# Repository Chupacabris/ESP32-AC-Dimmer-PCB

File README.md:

# ESP32-AC-Dimmer-PCB

Kicad project for ESP32-based PCB board designed to dim three AC outputs using triacs triggered at a set time after zero-crossing detection (ZCD).

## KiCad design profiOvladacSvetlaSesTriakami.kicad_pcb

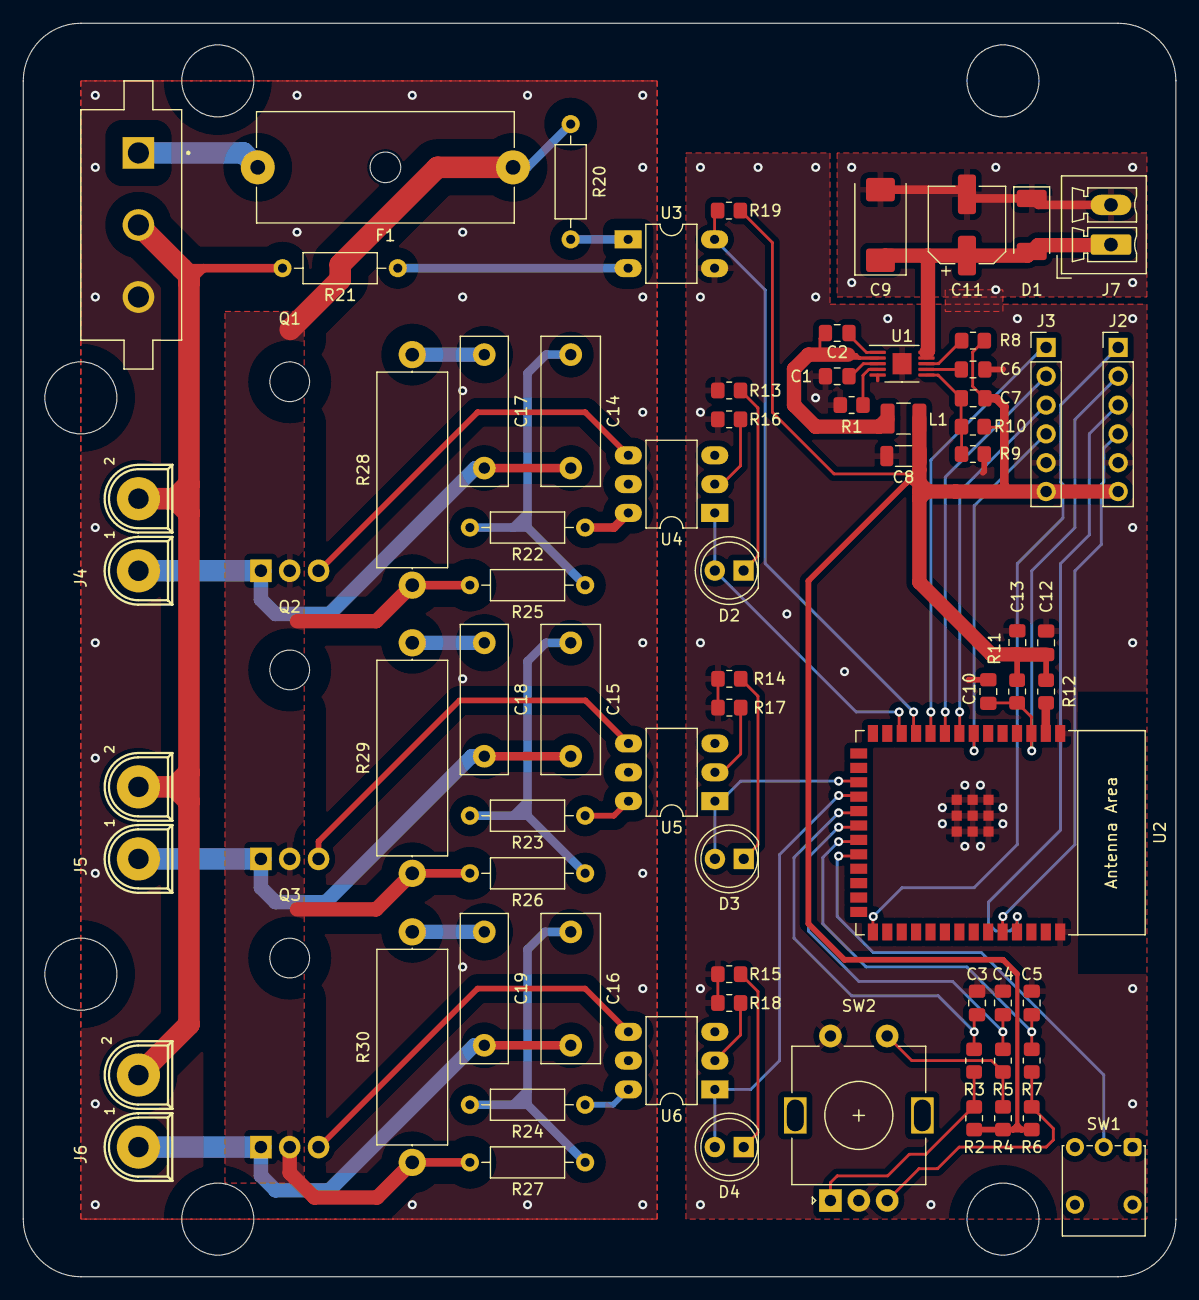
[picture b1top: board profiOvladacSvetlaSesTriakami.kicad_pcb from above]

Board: 2 copper layers, 101.6 x 110.5 mm, 73 parts (0 on the bottom side), 56 nets.

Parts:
C1: 1uF/10V; C_0805_2012Metric_Pad1.18x1.45mm_HandSolder
C2: 0.1uF/10V; C_0805_2012Metric_Pad1.18x1.45mm_HandSolder
C3, C4, C5: 10n; C_0805_2012Metric_Pad1.18x1.45mm_HandSolder
C6: 10nF/10V; C_0805_2012Metric_Pad1.18x1.45mm_HandSolder
C7: 10pF; C_0805_2012Metric_Pad1.18x1.45mm_HandSolder
C8: 22uF/X7R; C_1206_3216Metric
C9: 4.7u; CP_EIA-7343-15_Kemet-W
C10: 1uF; C_0805_2012Metric_Pad1.18x1.45mm_HandSolder
C11: 100u; CP_Elec_6.3x7.7
C12: 10uF; C_0805_2012Metric_Pad1.18x1.45mm_HandSolder
C13: 0.1uF; C_0805_2012Metric_Pad1.18x1.45mm_HandSolder
C14, C15, C16: 0.05uF; C_Rect_L13.0mm_W5.0mm_P10.00mm_FKS3_FKP3_MKS4
C17, C18, C19: 0.01uF; C_Rect_L13.0mm_W4.0mm_P10.00mm_FKS3_FKP3_MKS4
D1: DIODE; D_2010_5025Metric_Pad1.52x2.65mm_HandSolder
D2, D3, D4: LED; LED_D5.0mm
F1: Fuse; Fuseholder_Cylinder-5x20mm_Schurter_0031_8201_Horizontal_Op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
J1: 350429-1; TE_350429-1
J2: programovaci; PinHeader_1x06_P2.54mm_Vertical
J3: GPIOs; PinHeader_1x06_P2.54mm_Vertical
J4, J5, J6: 350428-1
J7: Conn_01x02_Socket; PhoenixContact_MCV_1,5_2-G-3.5_1x02_P3.50mm_Vertical
L1: 2.2uH; L_1210_3225Metric
Q1, Q2, Q3: BT138; TO-220-3_Horizontal_TabDown
R1: 18.2k; R_0805_2012Metric_Pad1.20x1.40mm_HandSolder
R2, R3, R4, R5, R6, R7, R11, R19: 10k; R_0805_2012Metric_Pad1.20x1.40mm_HandSolder
R8: 100k; R_0805_2012Metric_Pad1.20x1.40mm_HandSolder
R9: 309K; R_0805_2012Metric_Pad1.20x1.40mm_HandSolder
R10: 1M; R_0805_2012Metric_Pad1.20x1.40mm_HandSolder
R12: 0; R_0805_2012Metric_Pad1.20x1.40mm_HandSolder
R13, R14, R15, R16, R17, R18: 470; R_0805_2012Metric_Pad1.20x1.40mm_HandSolder
R20, R21: 33k; R_Axial_DIN0207_L6.3mm_D2.5mm_P10.16mm_Horizontal
R22, R23, R24: 360; R_Axial_DIN0207_L6.3mm_D2.5mm_P10.16mm_Horizontal
R25, R26, R27: 470; R_Axial_DIN0207_L6.3mm_D2.5mm_P10.16mm_Horizontal
R28, R29, R30: 39; R_Axial_DIN0617_L17.0mm_D6.0mm_P20.32mm_Horizontal
SW1: SW_SPDT; SW_Push_1P2T_Vertical_E-Switch_800UDP8P1A1M6
SW2: RotaryEncoder_Switch; RotaryEncoder_Alps_EC11E-Switch_Vertical_H20mm
U1: LT8608; MSOP-10-1EP_3x3mm_P0.5mm_EP1.68x1.88mm
U2: ESP32-S3-WROOM-1
U3: LTV-814; DIP-4_W7.62mm_LongPads
U4, U5, U6: MOC3021M; DIP-6_W7.62mm_LongPads

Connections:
+3.3V: C7.2, C8.1, C12.2, C13.1, J2.6, J3.6, L1.1, R2.1, R4.1, R6.1, R8.1, R10.1, R11.1, R12.1, R19.1
A: C3.1, R3.2, U2.19 (GPIO11/TOUCH11/ADC2_CH0/FSPID/FSPIIO5/S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)
B: C5.1, R7.2, U2.21 (GPIO13/TOUCH13/ADC2_CH2/FSPIQ/FSPIIO7/S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)
CTS: J2.1, U2.27 (GPIO0/BOOT)
GND: C1.2, C3.2, C4.2, C5.2, C6.2, C8.2, C9.2, C10.2, C11.2, C12.1, C13.2, D1.1 (K), J2.5, J3.5, J7.2, R1.1, R9.1, R13.2, R14.2, R15.2, R16.1, R17.1, R18.1, SW1.1 (A), SW2.C, SW2.S2, U1.5 (SYNC), U1.11 (GND), U2.1 (GND), U2.40 (GND), U2.41 (GND), U3.3
GPIO7: J3.4, U2.7 (GPIO7/TOUCH7/ADC1_CH6)
GPIO15: J3.3, U2.8 (GPIO15/U0RTS/ADC2_CH4/XTAL_32K_P)
GPIO16: J3.2, U2.9 (GPIO16/U0CTS/ADC2_CH5/XTAL_32K_N)
GPIO17: J3.1, U2.10 (GPIO17/U1TXD/ADC2_CH6)
L: F1.2, J1.1
L-zaPoistku: F1.1, Q1.2 (A2), Q2.2 (A2), Q3.2 (A2), R20.2, R25.2, R26.2, R27.2, R28.1, R29.1, R30.1
unnamed: C14.1, R22.2, R25.1
unnamed: C15.1, R23.2, R26.1
unnamed: C16.1, R24.2, R27.1
unnamed: C17.1, R28.2
unnamed: C18.1, R29.2
unnamed: C19.1, R30.2
unnamed: D2.1 (K), R13.1
unnamed: D3.1 (K), R14.1
unnamed: D4.1 (K), R15.1
unnamed: C14.2, C17.2, J4.1, Q1.1 (A1)
unnamed: Q1.3 (G), U4.4
unnamed: C15.2, C18.2, J5.1, Q2.1 (A1)
unnamed: Q2.3 (G), U5.4
unnamed: C16.2, C19.2, J6.1, Q3.1 (A1)
unnamed: Q3.3 (G), U6.4
unnamed: R2.2, R3.1, SW2.A
unnamed: R4.2, R5.1, SW2.S1
unnamed: R6.2, R7.1, SW2.B
unnamed: R16.2, U4.2
unnamed: R17.2, U5.2
unnamed: R18.2, U6.2
unnamed: R20.1, U3.1
unnamed: R21.1, U3.2
unnamed: R22.1, U4.6
unnamed: R23.1, U5.6
unnamed: R24.1, U6.6
unnamed: C2.1, U1.1 (BST)
unnamed: C7.1, R9.2, R10.2, U1.6 (FB)
unnamed: C1.1, U1.3 (INTVCC)
unnamed: R8.2, U1.8 (PG)
unnamed: R1.2, U1.4 (RT)
unnamed: C2.2, L1.2, U1.2 (SW)
unnamed: C6.1, U1.7 (TR/SS)
unnamed: R12.2, U2.2 (3V3)
Nulak: J1.2, J4.2, J5.2, J6.2, R21.2
RTS: C10.1, J2.2, R11.2, U2.3 (EN)
RXD: J2.4, U2.36 (U0RXD/GPIO44/CLK_OUT2)
SW: C4.1, R5.2, U2.20 (GPIO12/TOUCH12/ADC2_CH1/FSPICLK/FSPIIO6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)
Spustac1: D2.2 (A), U2.12 (GPIO8/TOUCH8/ADC1_CH7/SUBSPICS1), U4.1
Spustac2: D3.2 (A), U2.17 (GPIO9/TOUCH9/ADC1_CH8/FSPIHD/SUBSPIHD), U5.1
Spustac3: D4.2 (A), U2.18 (GPIO10/TOUCH10/ADC1_CH9/FSPICS0/FSPIIO4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), U6.1
TXD: J2.3, U2.37 (U0TXD/GPIO43/CLK_OUT1)
VCC: C9.1, C11.1, D1.2 (A), J7.1, U1.9 (VIN), U1.10 (EN/UV)
ZCDet: R19.2, U2.11 (GPIO18/U1RXD/ADC2_CH7/CLK_OUT3), U3.4
mode_SW: SW1.2 (B), U2.22 (GPIO14/TOUCH14/ADC2_CH3/FSPIWP/FSPIDQS/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)
